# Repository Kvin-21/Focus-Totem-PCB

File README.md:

# Focus Totem

A desk totem that runs a Pomodoro/study timer. Twist the encoder to dial in the minutes, press to start, and the two side LEDs breathe along with the session -
amber while setting up, green while the clock is running, red for the last minute, and then a flash when done. The OLED shows the live countdown and where you are (FOCUS / BREAK / DONE).

It's a 4-input hackpad built around a through-hole Seeed XIAO RP2040 and runs QMK, so it doubles as a tiny macropad.

## Controls

| Input          | Does                                  |
|----------------|---------------------------------------|
| Encoder turn   | Set the minutes                       |
| Encoder press  | Start / pause (same as Key 1)         |
| Key 1          | Start / pause                         |
| Key 2          | Hold to reset to the set time         |
| Key 3          | Cycle the short-break preset          |

## Schematic

## PCB

Two-layer, 84 × 72 mm, ground pour both sides, M3 mounting holes in the corners. The XIAO is through-hole and mounts on the **bottom**, so the macropad is assembled from underneath and its USB port lines up with the slot in the case.

| Top | Bottom |
|-----|--------|
|  |  |

## Case

A 3D-printed sandwich: a switch **plate** on top (the switches clip in, the encoder bush and OLED poke through, the side LEDs show through two little windows), the PCB in the middle, and a **bottom tray** that the XIAO tucks into with a USB slot in the back wall. Four M3 screws drop in from the top, through the plate and PCB, into tapped standoffs in the tray. Every pocket has 0.4 mm of clearance per side, and "FOCUS TOTEM" is engraved into the plate.

Both parts print flat with **no supports** — the plate face-up, the tray floor-down. The USB slot has a 45° self-supporting roof so nothing bridges.

## Bill of materials

| Ref      | Part                                   | Notes                        | Qty |
|----------|----------------------------------------|------------------------------|-----|
| U1       | Seeed XIAO RP2040 (through-hole)       | the brains                   | 1   |
| SW1–SW3  | MX-compatible switch                   | the three keys               | 3   |
| SW4      | Alps EC11 rotary encoder (with switch) | dial + push                  | 1   |
| J1       | 0.91" SSD1306 OLED, 128×32, I²C        | 4-pin module                 | 1   |
| D1, D2   | SK6812 MINI-E                          | addressable RGB              | 2   |
| R1, R2   | 4.7 kΩ, 0805                           | I²C pull-ups                 | 2   |
| R3       | 470 Ω, 0805                            | series on the LED data line  | 1   |
| C1       | 100 nF, 0805                           | OLED decoupling              | 1   |
| C2       | 10 µF, 0805                            | LED bulk                     | 1   |
| H1–H4    | M3 × 14 screw                          | sandwich the stack           | 4   |

## Wiring / pinout

| Pad  | RP2040 | Goes to                    |
|------|--------|----------------------------|
| D0   | GP26   | Key 1                      |
| D1   | GP27   | Key 2                      |
| D2   | GP28   | Key 3                      |
| D3   | GP29   | Encoder switch             |
| D4   | GP6    | OLED SDA (I²C1)            |
| D5   | GP7    | OLED SCL (I²C1)            |
| D6   | GP0    | Encoder A                  |
| D7   | GP1    | Encoder B                  |
| D10  | GP3    | SK6812 data in             |
| 5V   | —      | LED V+, C2                 |
| 3V3  | —      | OLED V+, I²C pull-ups, C1  |
| GND  | —      | common ground              |

Each key and the encoder switch pull their pin to ground. The encoder common goes to ground. The LEDs are daisy-chained XIAO → R3 → D1 → D2. The OLED answers on I²C address `0x3C`.

## Repository layout

```
CAD/         the assembled model — focus-totem.3mf (whole macropad, one file)
PCB/         KiCad project — schematic, routed board, libraries
Firmware/    QMK keyboard (keyboard.json, config.h, rules.mk, keymaps/)
production/  gerbers.zip, plate + bottom STLs, firmware.uf2, case source (.scad)
assets/      the screenshots above
```

## Firmware — build & flash

The firmware is a QMK keyboard. Drop the `Firmware` folder into a QMK checkout as a keyboard called `focus_totem` and build it:

```sh
# from the root of a qmk_firmware checkout
cp -r Firmware <qmk_firmware>/keyboards/focus_totem
qmk compile -kb focus_totem -km default
```

To flash: plug the XIAO in, double-tap its reset/boot so it mounts as a USB drive, and copy the `.uf2` across. It reboots into the firmware on its own.

## Case — regenerating the model

The case is parametric OpenSCAD ([`production/focus-totem.scad`](production/focus-totem.scad)), driven off the board outline and the KiCad component positions:

```sh
cd production
openscad -D 'part="plate"'    -o focus-totem-plate.stl  focus-totem.scad
openscad -D 'part="bottom"'   -o focus-totem-bottom.stl focus-totem.scad
openscad -D 'part="assembly"' -o ../CAD/focus-totem.3mf focus-totem.scad
```

Print the plate and bottom flat, no supports; PLA or PETG at 0.2 mm is fine.

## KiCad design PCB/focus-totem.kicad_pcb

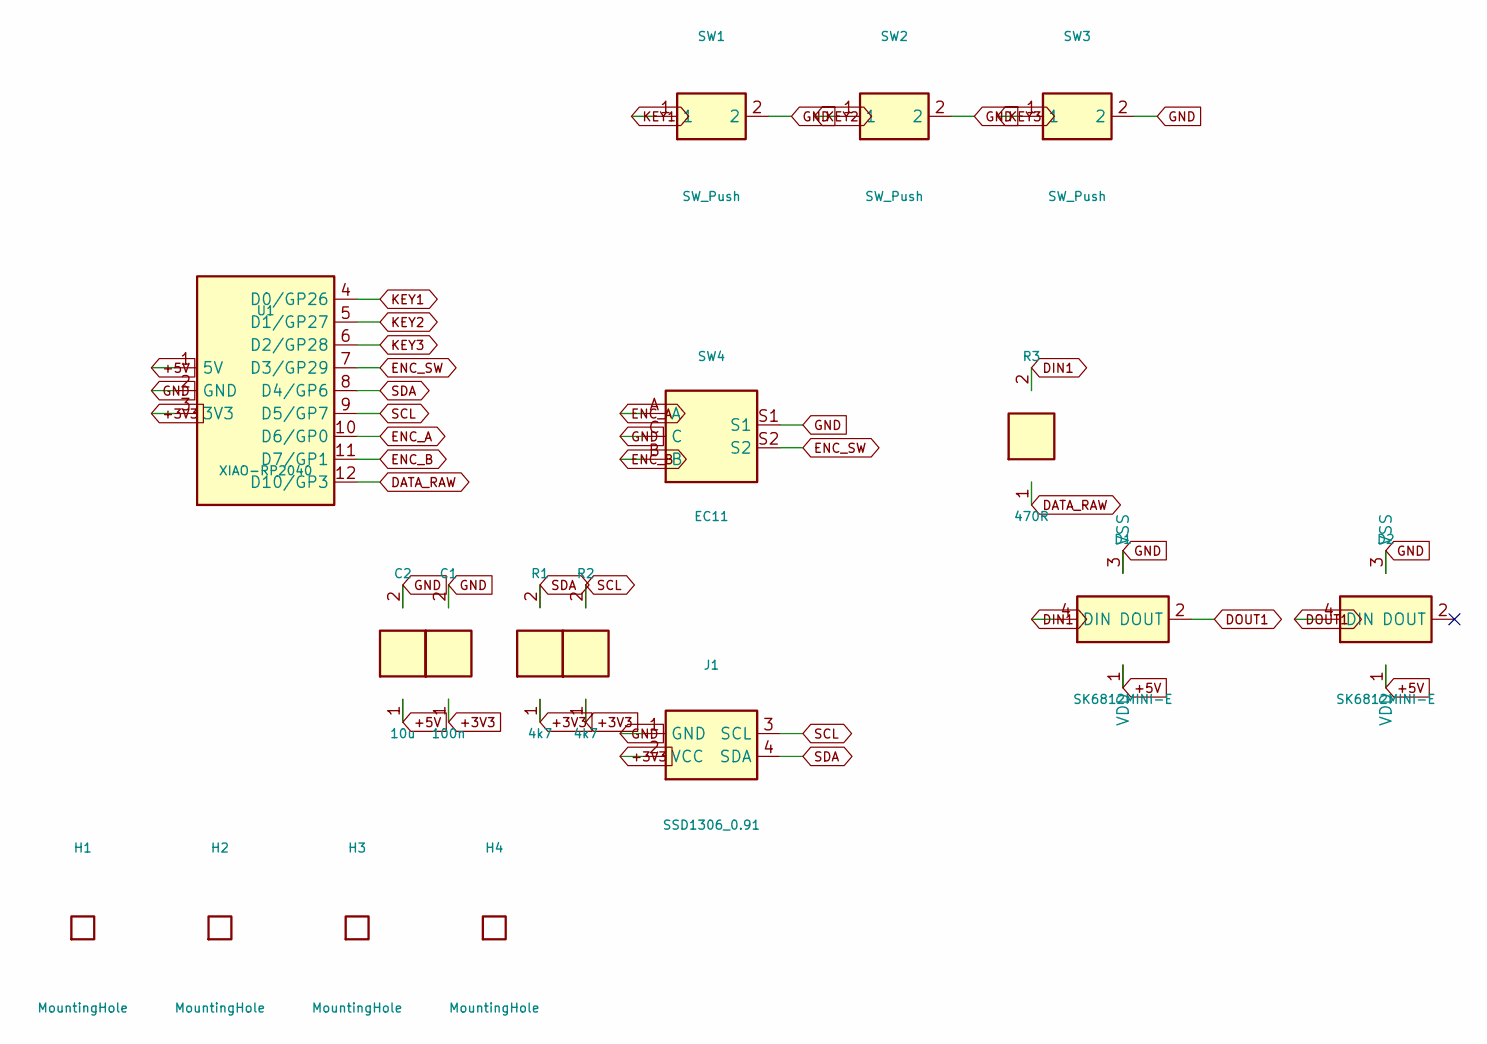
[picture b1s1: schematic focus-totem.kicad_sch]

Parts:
C1: 100n; C_0805_2012Metric
C2: 10u; C_0805_2012Metric
D1, D2: SK6812MINI-E
H1, H2, H3, H4: MountingHole; MountingHole_3.2mm_M3
J1: SSD1306_0.91; PinHeader_1x04_P2.54mm_Vertical
R1, R2: 4k7; R_0805_2012Metric
R3: 470R; R_0805_2012Metric
SW1, SW2, SW3: SW_Push; SW_Cherry_MX_1.00u_PCB
SW4: EC11; RotaryEncoder_Alps_EC11E-Switch_Vertical_H20mm
U1: XIAO-RP2040

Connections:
+3V3: C1.1, J1.2 (VCC), R1.1, R2.1, U1.3 (3V3)
+5V: C2.1, D1.1 (VDD), D2.1 (VDD), U1.1 (5V)
DATA_RAW: R3.1, U1.12 (D10/GP3)
DIN1: D1.4 (DIN), R3.2
DOUT1: D1.2 (DOUT), D2.4 (DIN)
ENC_A: SW4.A, U1.10 (D6/GP0)
ENC_B: SW4.B, U1.11 (D7/GP1)
ENC_SW: SW4.S2, U1.7 (D3/GP29)
GND: C1.2, C2.2, D1.3 (VSS), D2.3 (VSS), J1.1 (GND), SW1.2, SW2.2, SW3.2, SW4.C, SW4.S1, U1.2 (GND)
KEY1: SW1.1, U1.4 (D0/GP26)
KEY2: SW2.1, U1.5 (D1/GP27)
KEY3: SW3.1, U1.6 (D2/GP28)
SCL: J1.3 (SCL), R2.2, U1.9 (D5/GP7)
SDA: J1.4 (SDA), R1.2, U1.8 (D4/GP6)

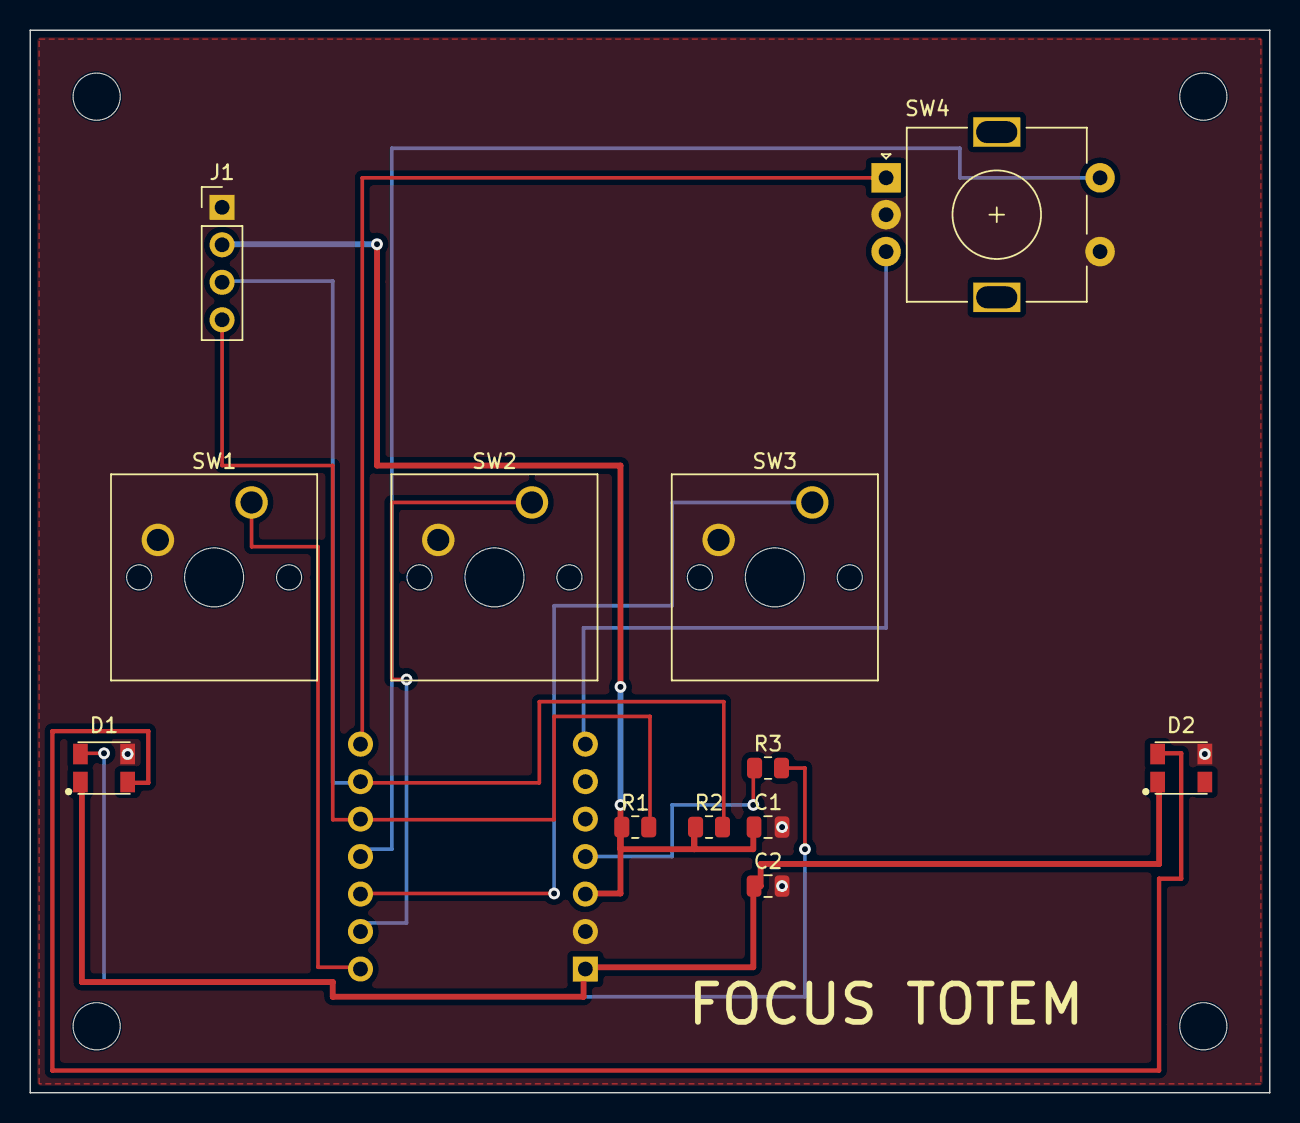
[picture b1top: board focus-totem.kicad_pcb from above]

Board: 2 copper layers, 84.0 x 72.0 mm, 17 parts (1 on the bottom side), 14 nets.

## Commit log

2026-06-10 Added initial PCB and firmware
2026-06-11 Added Pomodoro timer, RGB/OLED, and updates
2026-06-11 Add case files and update README
    Add the case TLs (plate + bottom), and updated Readme
2026-06-11 Update Reamde
    Added images
2026-06-11 Update Readme
    Added images
2026-06-12 Add PCB, CAD and production files
    Added full KiCad board (PCB/focus-totem.kicad_pcb), footprints and symbols, and XIAO/RGB LED footprint + reorganised files
2026-06-12 Add production firmware.uf2
    Added the compiled UF2 firmware binary
2026-06-12 Update to files and images
